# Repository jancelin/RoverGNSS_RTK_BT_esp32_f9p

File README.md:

> experimental code!!!

### This code allows you to connect an esp32 coupled to a Ublox F9P GNSS module on the UART port to use NTRIP clients on smartphones such as:
* [Lefebure](https://play.google.com/store/apps/details?id=com.lefebure.ntripclient) 	:white_check_mark:
* [BTGNSS](https://play.google.com/store/apps/details?id=com.clearevo.bluetooth_gnss) 	:white_check_mark:
* [SwMpas](https://play.google.com/store/apps/details?id=np.com.softwel.swmaps) 	:white_check_mark:

## Param Arduino IDE

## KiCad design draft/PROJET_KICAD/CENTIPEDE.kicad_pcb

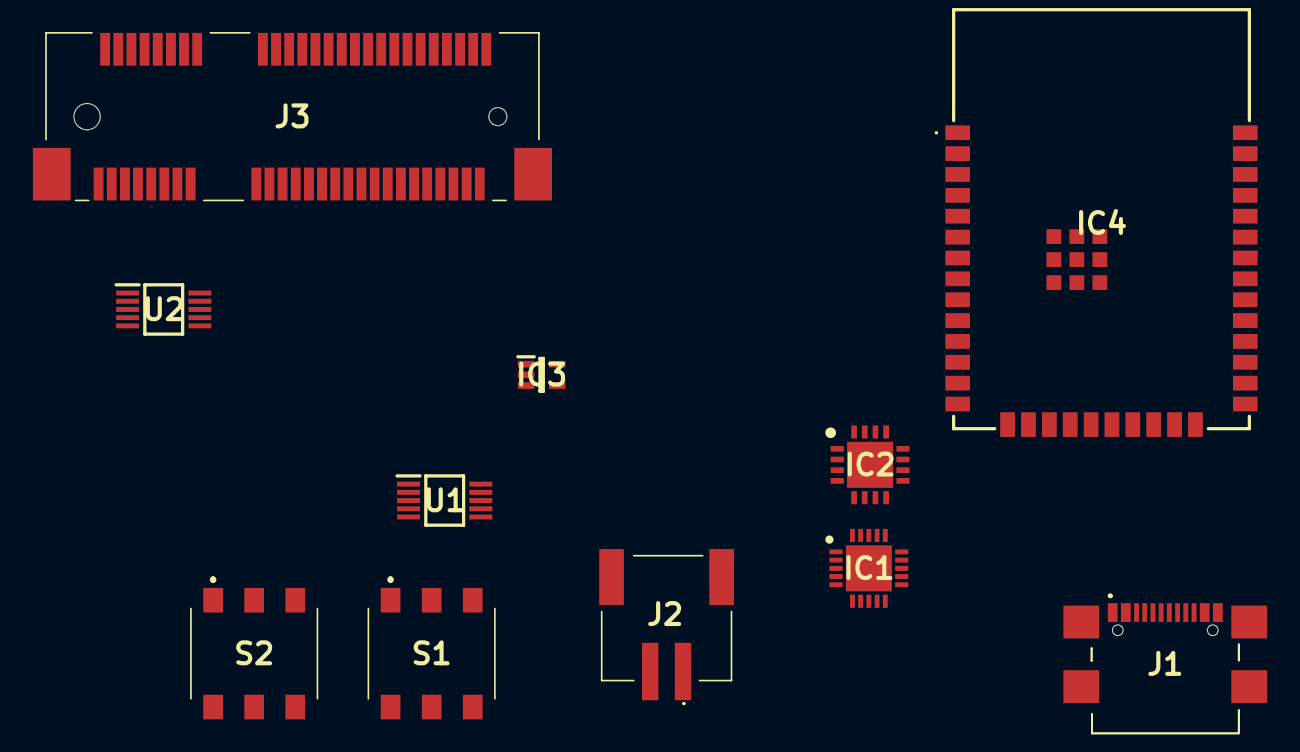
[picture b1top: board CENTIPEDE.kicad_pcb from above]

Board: 2 copper layers, 11 parts (0 on the bottom side), 2 nets, no tracks yet.

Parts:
IC1: MCP73871-2CCI_ML; QFN50P400X400X100-21N-D
IC2: TPS61090RSAR; QFN65P400X400X100-17N
IC3: SC573V33RTRC; SOT65P210X110-5N
IC4: ESP32-WROOM-32E-N8; ESP32WROOM32EN8
J1: USB4110-GF-A; USB4110GFA
J2: S2B-PH-SM4-TB_LF__SN_; S2BPHSM4TBLFSN
J3: 67910-0002; 67910-5700
S1, S2: 452403012014
U1, U2: FSUSB42MUX; SOP50P490X110-10N

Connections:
5V_USB_C: J1.A4, J1.A9, J1.B4, J1.B9
GND: J1.A1, J1.A12, J1.B1, J1.B12, J1.MP1, J1.MP2, J1.MP3, J1.MP4

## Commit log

2023-01-24 adapt 2 arduino ide, modify uart1 txrx for running with pflite
2023-01-24 add config for f9p UART1: RTCM3 in / NMAE output 5hz
2023-01-24 add config for IDE arduino
2023-01-24 add licence
2023-01-24 add readme
2023-01-24 experimental!!!
2023-11-20 Create draft.md for rover rtk v6
2023-11-30 kicad project added for pcb rtk rover v6
2023-11-30 Correct errors on supply schematic
2024-02-27 Update with F9P MicroPci
2024-02-29 rename files
2024-02-29 add ref composants
2024-02-29 param arduino ide
2024-02-29 upd config f9p
2024-02-29 add firmware upd f9p
2024-02-29 less cable upd f9p receiver over wifi with U-center
2024-03-19 Adding POWER_PIN variable
2024-03-19 Update full use of debug_log
2024-03-19 Update comments
2024-09-18 clear lilygo
